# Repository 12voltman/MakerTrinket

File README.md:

# MakerTrinket
Through hole remix of Adafruit's excellent Trinket development boards

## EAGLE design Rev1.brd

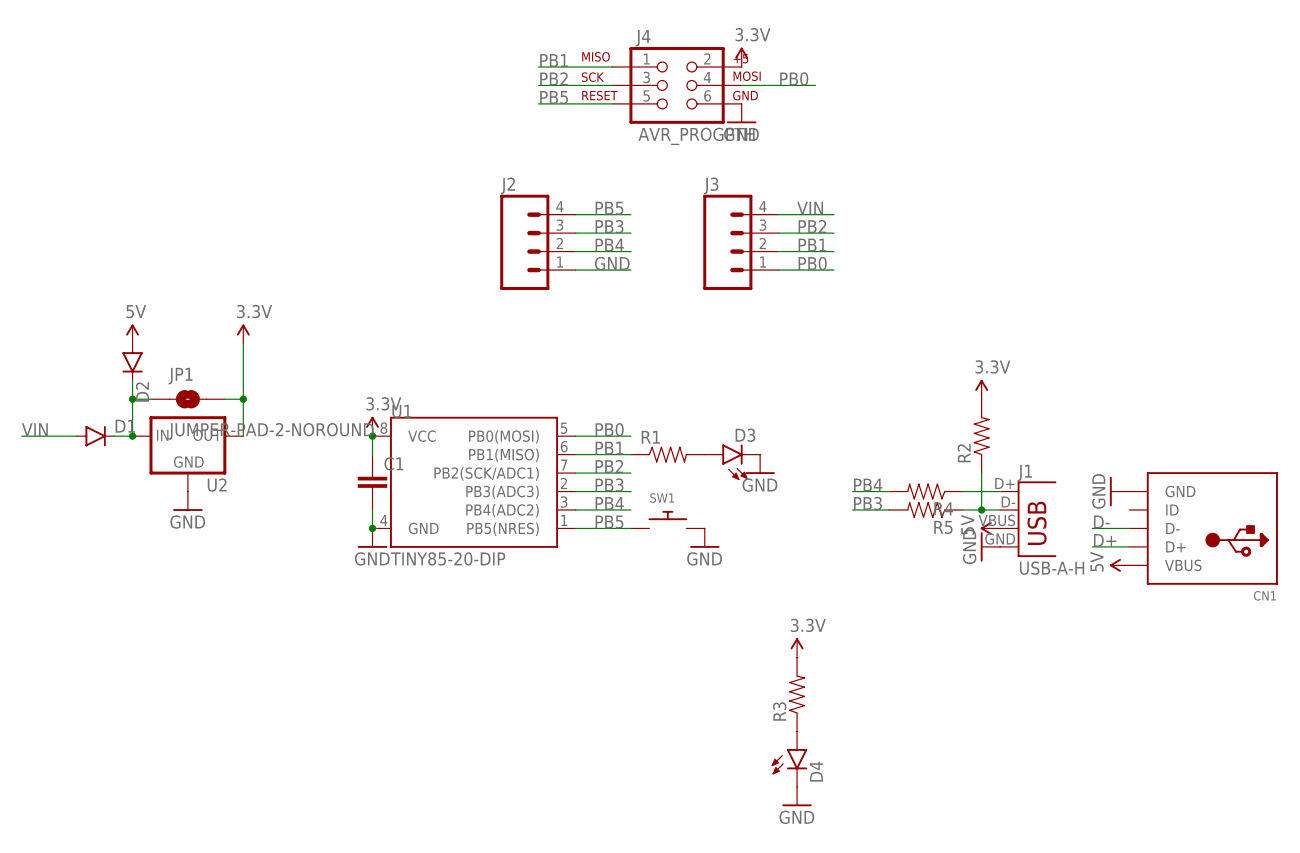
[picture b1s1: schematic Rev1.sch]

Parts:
C1: 0.1UF-50V-20%(PTH)KIT-EZ; CAP-PTH-SMALL-KIT
CN1: USBTHM; USB-MINIB-THM
D1, D2: DIODEPTH; DIODE-1N4001
D3, D4: LED3MM
J1: USB-A-H
J2, J3: M04PTH; 1X04
J4: AVR_PROGPTH; 2X3
JP1: JUMPER-PAD-2-NOROUND; PAD-JUMPER-2-NO_YES_SILK_ROUND
R1, R2, R3, R4, R5: RESISTORPTH-1/6W; 1/6W-RES
SW1: SWITCH_PUSHBUTTONEVQ-PE; TACT_PANA-EVQ
U1: TINY85-20-DIP; DIP08
U2: V_REG_78XXTO-92_UNTESTED; TO-92

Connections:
3.3V: C1.1, J4.2 (VIN), JP1.2, R2.2, R3.2, U1.8 (VCC), U2.1 (OUT)
5V: CN1.VBUS, D2.A, J1.VBUS
D+: CN1.D+, J1.D+, R4.1
D-: CN1.D-, J1.D-, R2.1, R5.1
GND: C1.2, CN1.GND, D3.K (C), D4.K (C), J1.GND, J2.1, J4.6 (GND), SW1.P$2, U1.4 (GND), U2.2 (GND)
unnamed: D4.A, R3.1
unnamed: D3.A, R1.2
unnamed: D1.C, D2.C, JP1.1, U2.3 (IN)
PB0: J3.1, J4.4 (MOSI), U1.5 (PB0(MOSI))
PB1: J3.2, J4.1 (MISO), R1.1, U1.6 (PB1(MISO))
PB2: J3.3, J4.3 (SCK), U1.7 (PB2(SCK/ADC1))
PB3: J2.3, R5.2, U1.2 (PB3(ADC3))
PB4: J2.2, R4.2, U1.3 (PB4(ADC2))
PB5: J2.4, J4.5 (RESET), SW1.P$1, U1.1 (PB5(NRES))
VIN: D1.A, J3.4

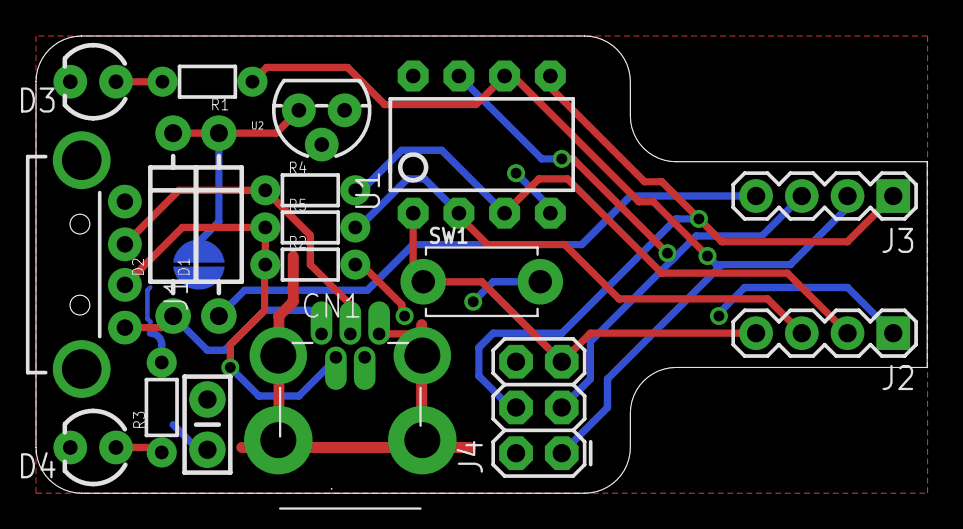
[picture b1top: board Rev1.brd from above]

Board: 2 copper layers, 49.5 x 25.4 mm, 19 parts (1 on the bottom side), 15 nets.

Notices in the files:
parts and their libraries:
SparkFun-LED: Licensing: Creative Commons ShareAlike 4.0 International - https://creativecommons.org/licenses/by-sa/4.0
